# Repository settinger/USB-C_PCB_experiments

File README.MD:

# USB-C PCB Experiments

This is part of an ongoing series of projects involving creative interpretations of the USB mechanical standards. You've probably seen [2.0mm thick PCBs that fit in USB ports](http://digistump.com/products/1), and maybe you've seen [0.6mm thick PCBs that fit in USB-Micro cables](https://twitter.com/DHammarskjold/status/1285291152602796032). So what about USB-C? T​he plastic tab inside a USB-C port is about 0.7mm thick. I think [bobricius](https://hackaday.io/bobricius) has had success using 0.8mm thick PCBs; 0.6mm thick PCBs are way too loose. I haven't found a fab that will do 0.7mm (or 28 mil) PCBs unless you special-order an entire panel.​

So, what other ways are there to reach 0.7mm thickness? My original plan was to join an 0.1mm flex PCB and an 0.6mm FR4 PCB, but then I realized: you know what else is 0.6mm thick? The ATtiny84A BGA package. Granted, there are only contacts on one side of the PCB, but that shouldn't matter with the symmetric USB-C pinout, right? ...Right? (foreshadowing)

The 3mm-square ATtiny acts as a stiffener for the flex PCB, and it comes out to 0.7mm on the dot! I only have an imperial set of calipers as seen above. The dial shows 0.0275 inches, which is 0.6985 millimeters. ~~So this is looking pretty promising.~~ After [my initial tests](https://twitter.com/DHammarskjold/status/1476667605746270224), I am leaning toward a circuit sandwiched between two PCBs. The result is about 0.85mm thick with OSH Park flex PCBs, so I may need to locate another vendor.

What would you do with an ATtiny that lives inside your USB-C cable? I have a few ideas for demonstrations at the moment.

## Demo 1: RGB LED that can't be programmed over USB

There are two revisions of this design; the schematics are in the repo as `rgb_no_bootloader.kicad_sch` and `rgb_no_bootloader_r2.kicad_sch`. Revision 1 is the one that I have assembled and ready to work with, it's also the one I would like some code help with! My current code is in the in the code folder as `demo_1_revision_1`; it is saved as an Arduino .ino file but it should work fine with AVR-GCC without any changes.

This demo is as simple as possible: the microcontroller controlls an RGB LED that juuuust barely pokes out of the USB-C cable plug. It has to be programmed using that 8-pin FFC connector, and then the FFC connector has to be snipped off in order to use the dang thing. Right now I have one fully-soldered version of revision 1, ~~but I haven't cut the FFC connector yet because I would like some help improving the code.~~

Demo 1 Revision 2 is necessary because, on revision 1, the RGB LED is *not* connected to the Fast-PWM-enabled pins on the microcontroller. As a result I have to use [binary code modulation](http://www.batsocks.co.uk/readme/art_bcm_3.htm) to achieve any sort of brightness control. It's working alright, [as shown here](https://twitter.com/DHammarskjold/status/1475741148522049536), ~~but I'm not confident enough with the code to chop off the programming connector yet.~~

When I finally removed the connector, I documented it [in this Twitter thread](https://twitter.com/DHammarskjold/status/1476667605746270224). I got excited and tried putting it in a powered USB cable while the top side was exposed. Unsurprisingly, this caused some shorts and some damage! I soldered in a new RGB LED and applied conformal coating. The conformal coating helped for a little while, but got scraped away pretty quickly. This suggests to me that any future designs will need to be sandwiched between *two* PCBs.

As you can see, there is a large tab sticking out so I can grab and remove the PCB from the cable. However, out of spite for, uh, myself, I have labelled it the "cowards' tab." Past me was encouraging present me to remove that tab and make the board impossible to remove, thereby turning a useful cable into a cute little art piece for all eternity.

## Demo 2: ~~R~~GB LED that *can* be programmed over USB

It would be nice to use the USB data lines to program the microcontroller! I didn't attempt this for the first revision because I wanted to keep the board as uncluttered and simple as possible. It will result in a denser board that may need more careful soldering, but it should be possible! Well, *mostly* possible. I didn't find a way to route red green and blue at the same time, so I've omitted red from the design.

As I understand it, I need to add at least five extra components: a pullup for the D- line, small resistors on the D- and D+ lines, and zener diodes as level shifters. This is the low-complexity approach used on the Digispark and its derivatives. I have not attempted to make this board yet. Also, look at the 3d render above; doesn't it look like an owl? I love it.

There is an interesting issue, however. In the USB-C standard, the D+/D- lines are only connected on one side of the plug! It assumes that the USB-C port has D+/D- connectors on both sides, so the plug orientation should not matter. But our USB-C port only has D+/D- connectors on one side. We've reintroduced the classic USB behavior of having to flip the device over 3 times before it works!

## Demo 3: Basically a Digispark but smaller

In this version, the FFC portion is meant to stay attached! And all the components are 0402-sized with generous spacing so I can worry less when soldering. As a result it can be used in a slightly more "normal" fashion—still operable by sticking it inside a USB-C cable, but now there's a breakout of sorts.

## Demo 4: "Coulda used a 555"

On the Hackaday websites, "Coulda used a 555" is shorthand for grumpy commenters who criticize designs that they consider inelegant, for example, using a microcontroller where a 555 would suffice. In the past I've poked fun at this notion by, among other things, using *three* microcontrollers where a 555 would suffice, and using a 555 Schmitt Trigger where a single SPST button would suffice. As luck would have it, there is a BGA 555 IC that is just shy of 0.6mm tall! I've had to pair it with a 10μF capacitor that is a bit taller, but it's a fun idea to explore later.

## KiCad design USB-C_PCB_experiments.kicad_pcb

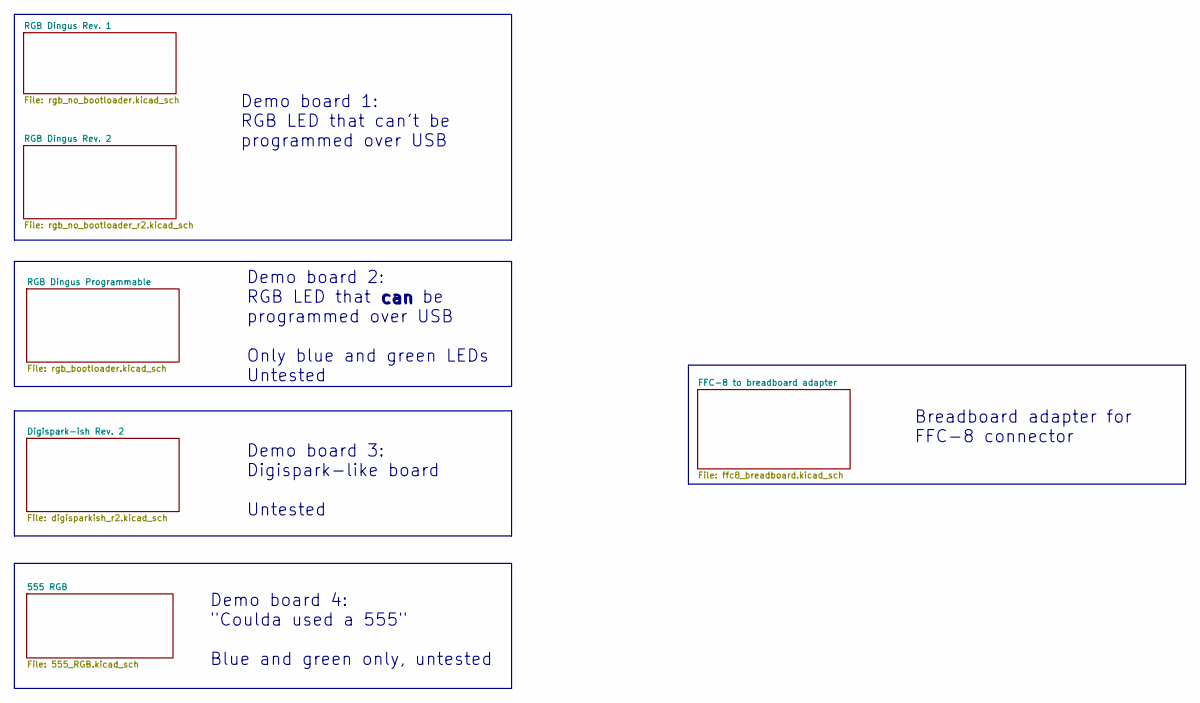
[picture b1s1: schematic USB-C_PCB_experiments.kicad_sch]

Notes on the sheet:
Breadboard adapter for FFC-8 connector
Demo board 1: RGB LED that can't be programmed over USB
Demo board 4: "Coulda used a 555" Blue and green only, untested
Demo board 3: Digispark-like board Untested
can
Demo board 2: RGB LED that can be programmed over USB Only blue and green LEDs Untested

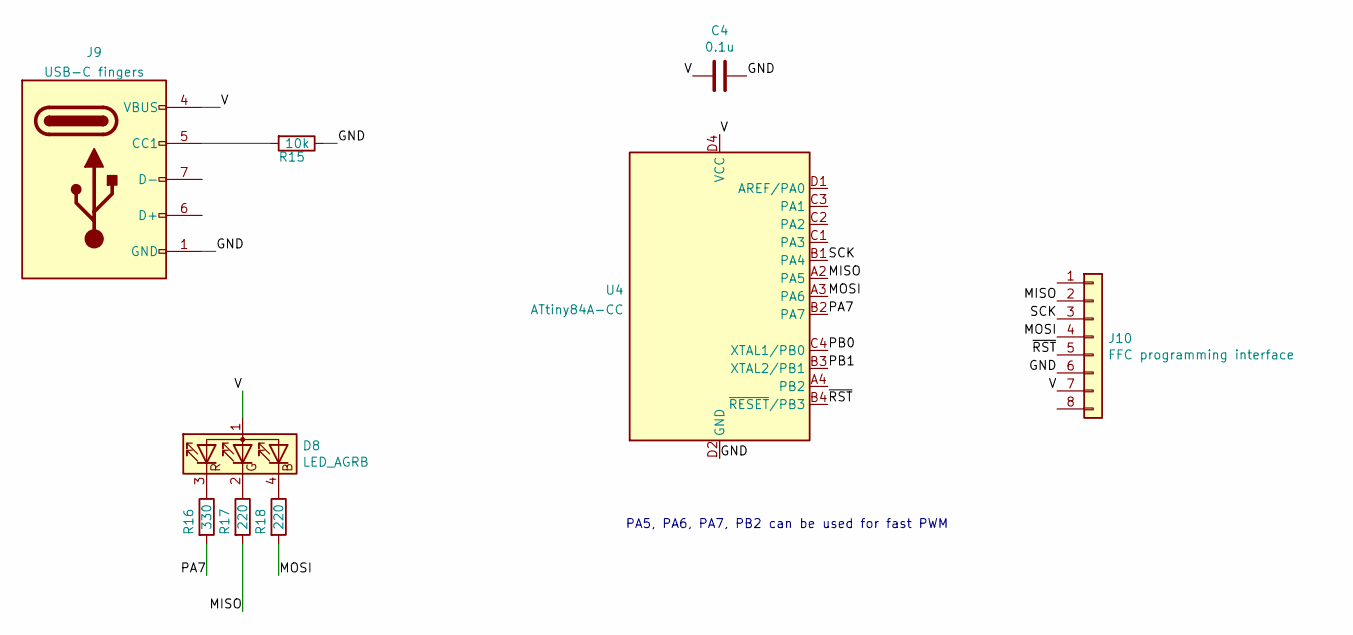
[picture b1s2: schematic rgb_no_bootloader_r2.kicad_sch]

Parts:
C4: 0.1u; C_0201_0603Metric
D8: LED_AGRB; LED_everlight_EASV2713RGBA1
J9: USB-C fingers
J10: FFC programming interface; FFC-08
R15: 10k; R_0201_0603Metric
R16: 330; R_0201_0603Metric
R17, R18: 220; R_0201_0603Metric
U4: ATtiny84A-CC; UFBGA-15_3.0x3.0mm_Layout4x4_P0.65mm

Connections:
/RGB Dingus Rev. 2/GND: C4.1, J9.1 (GND), J9.12 (GND), J10.6, R15.1, U4.D2 (GND), U4.D3 (GND)
/RGB Dingus Rev. 2/MISO: J10.2, R17.2, U4.A2 (PA5)
/RGB Dingus Rev. 2/MOSI: J10.4, R18.2, U4.A3 (PA6)
/RGB Dingus Rev. 2/PA7: R16.2, U4.B2 (PA7)
/RGB Dingus Rev. 2/PB0: U4.C4 (XTAL1/PB0)
/RGB Dingus Rev. 2/PB1: U4.B3 (XTAL2/PB1)
/RGB Dingus Rev. 2/SCK: J10.3, U4.B1 (PA4)
/RGB Dingus Rev. 2/V: C4.2, D8.1 (A), J9.4 (VBUS), J9.9 (VBUS), J10.7, U4.D4 (VCC)
/RGB Dingus Rev. 2/~RST: J10.5, U4.B4 (~RESET/PB3)
unnamed: D8.2 (GK), R17.1
unnamed: D8.3 (RK), R16.1
unnamed: D8.4 (BK), R18.1
unnamed: J9.5 (CC1), R15.2

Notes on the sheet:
PA5, PA6, PA7, PB2 can be used for fast PWM

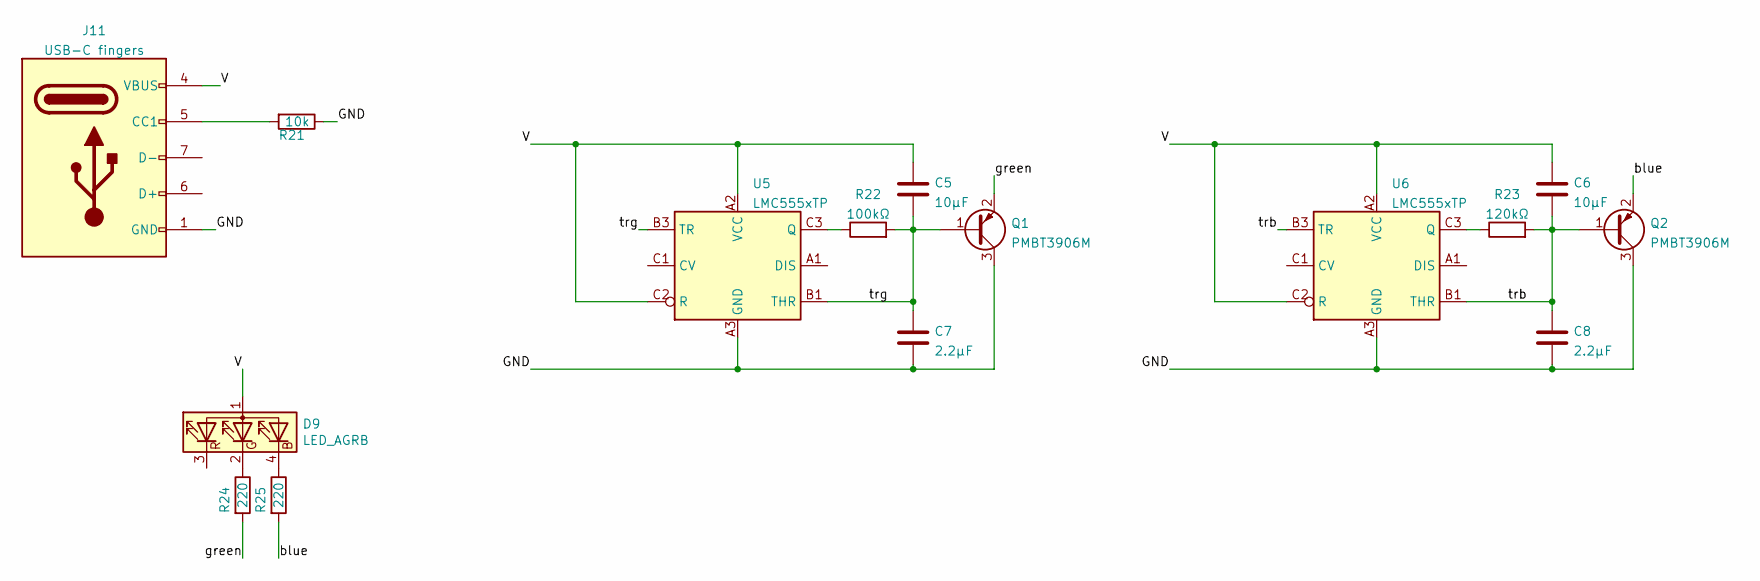
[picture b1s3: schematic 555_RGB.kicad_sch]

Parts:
C5, C6: 10μF; C_0402_1005Metric
C7, C8: 2.2μF; C_0201_0603Metric
D9: LED_AGRB; LED_everlight_EASV2713RGBA1
J11: USB-C fingers
Q1, Q2: PMBT3906M; SOT-883
R21: 10k; R_0201_0603Metric
R22: 100kΩ; R_0201_0603Metric
R23: 120kΩ; R_0201_0603Metric
R24, R25: 220; R_0201_0603Metric
U5, U6: LMC555xTP; Texas_DSBGA-8_1.43x1.41mm_Layout3x3_P0.5mm

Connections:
/555 RGB/GND: C7.2, C8.2, J11.1 (GND), J11.12 (GND), Q1.3 (C), Q2.3 (C), R21.1, U5.A3 (GND), U6.A3 (GND)
/555 RGB/V: C5.1, C6.1, D9.1 (A), J11.4 (VBUS), J11.9 (VBUS), U5.A2 (VCC), U5.C2 (R), U6.A2 (VCC), U6.C2 (R)
/555 RGB/blue: Q2.2 (E), R25.2
/555 RGB/green: Q1.2 (E), R24.2
/555 RGB/trb: C6.2, C8.1, Q2.1 (B), R23.2, U6.B1 (THR), U6.B3 (TR)
/555 RGB/trg: C5.2, C7.1, Q1.1 (B), R22.2, U5.B1 (THR), U5.B3 (TR)
unnamed: D9.2 (GK), R24.1
unnamed: D9.4 (BK), R25.1
unnamed: J11.5 (CC1), R21.2
unnamed: R22.1, U5.C3 (Q)
unnamed: R23.1, U6.C3 (Q)

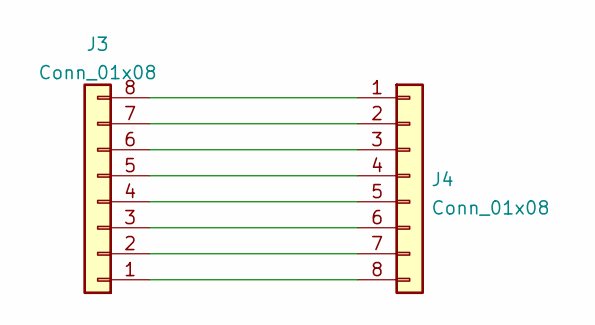
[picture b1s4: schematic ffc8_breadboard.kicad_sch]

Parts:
J3: Conn_01x08
J4: Conn_01x08; PinHeader_1x08_P2.54mm_Vertical

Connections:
unnamed: J3.1, J4.8
unnamed: J3.2, J4.7
unnamed: J3.3, J4.6
unnamed: J3.4, J4.5
unnamed: J3.5, J4.4
unnamed: J3.6, J4.3
unnamed: J3.7, J4.2
unnamed: J3.8, J4.1

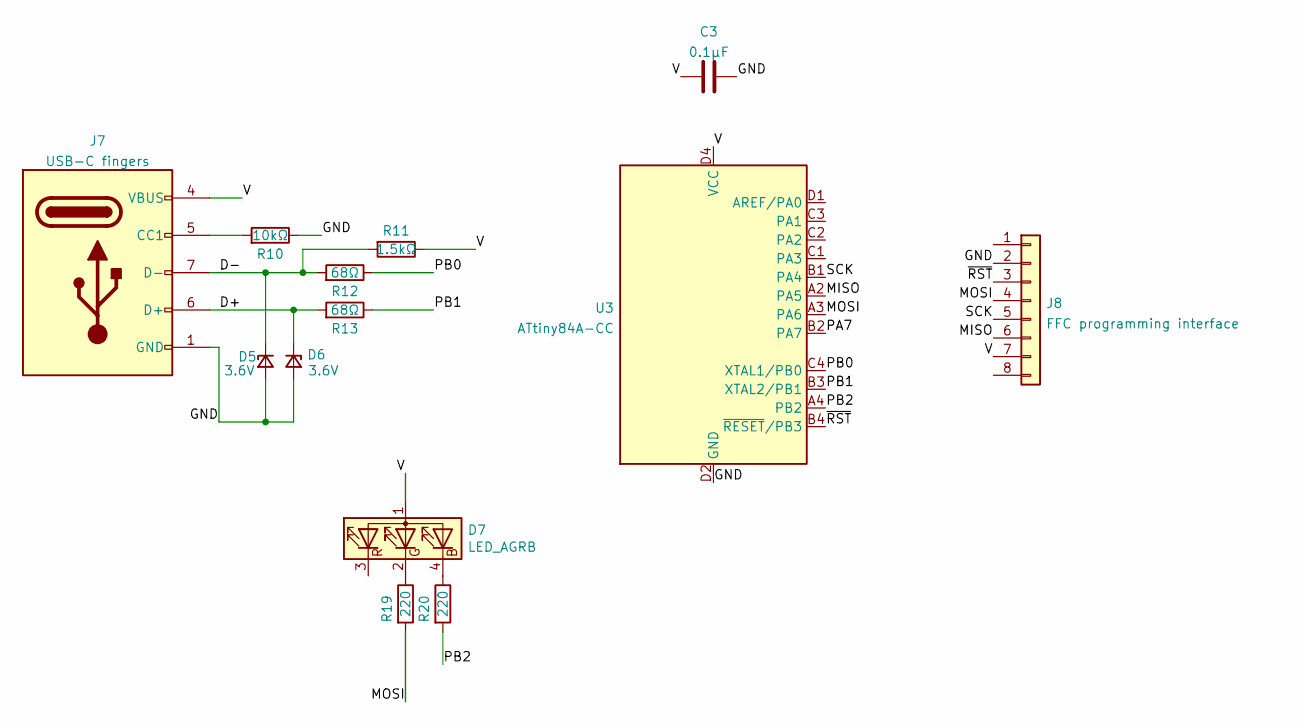
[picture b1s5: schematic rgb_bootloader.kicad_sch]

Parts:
C3: 0.1μF; C_0402_1005Metric
D5, D6: 3.6V; D_0402_1005Metric
D7: LED_AGRB; LED_everlight_EASV2713RGBA1
J7: USB-C fingers; usb-c-one-sided
J8: FFC programming interface; FFC-08
R10: 10kΩ; R_0402_1005Metric
R11: 1.5kΩ; R_0402_1005Metric
R12, R13: 68Ω; R_0402_1005Metric
R19, R20: 220; R_0201_0603Metric
U3: ATtiny84A-CC; UFBGA-15_3.0x3.0mm_Layout4x4_P0.65mm

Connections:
/RGB Dingus Programmable/D+: D6.1 (K), J7.6 (D+), R13.2
/RGB Dingus Programmable/D-: D5.1 (K), J7.7 (D-), R11.2, R12.2
/RGB Dingus Programmable/GND: C3.1, D5.2 (A), D6.2 (A), J7.1 (GND), J7.12 (GND), J8.2, R10.1, U3.D2 (GND), U3.D3 (GND)
/RGB Dingus Programmable/MISO: J8.6, U3.A2 (PA5)
/RGB Dingus Programmable/MOSI: J8.4, R19.2, U3.A3 (PA6)
/RGB Dingus Programmable/PA7: U3.B2 (PA7)
/RGB Dingus Programmable/PB0: R12.1, U3.C4 (XTAL1/PB0)
/RGB Dingus Programmable/PB1: R13.1, U3.B3 (XTAL2/PB1)
/RGB Dingus Programmable/PB2: R20.2, U3.A4 (PB2)
/RGB Dingus Programmable/SCK: J8.5, U3.B1 (PA4)
/RGB Dingus Programmable/V: C3.2, D7.1 (A), J7.4 (VBUS), J7.9 (VBUS), J8.7, R11.1, U3.D4 (VCC)
/RGB Dingus Programmable/~RST: J8.3, U3.B4 (~RESET/PB3)
unnamed: D7.2 (GK), R19.1
unnamed: D7.4 (BK), R20.1
unnamed: J7.5 (CC1), R10.2

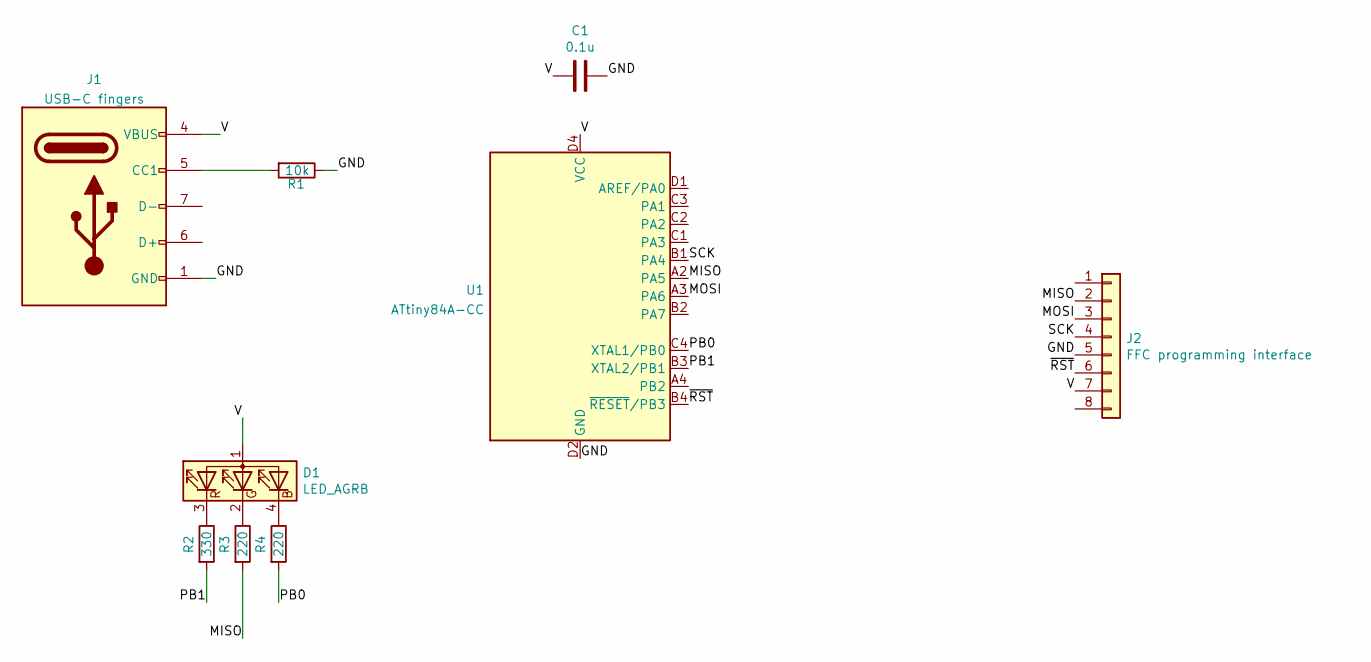
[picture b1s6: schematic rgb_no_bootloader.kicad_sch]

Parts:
C1: 0.1u; C_0201_0603Metric
D1: LED_AGRB; LED_everlight_EASV2713RGBA1
J1: USB-C fingers
J2: FFC programming interface; FFC-08
R1: 10k; R_0201_0603Metric
R2: 330; R_0201_0603Metric
R3, R4: 220; R_0201_0603Metric
U1: ATtiny84A-CC; UFBGA-15_3.0x3.0mm_Layout4x4_P0.65mm

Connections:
/RGB Dingus Rev. 1/GND: C1.1, J1.1 (GND), J1.12 (GND), J2.5, R1.1, U1.D2 (GND), U1.D3 (GND)
/RGB Dingus Rev. 1/MISO: J2.2, R3.2, U1.A2 (PA5)
/RGB Dingus Rev. 1/MOSI: J2.3, U1.A3 (PA6)
/RGB Dingus Rev. 1/PB0: R4.2, U1.C4 (XTAL1/PB0)
/RGB Dingus Rev. 1/PB1: R2.2, U1.B3 (XTAL2/PB1)
/RGB Dingus Rev. 1/SCK: J2.4, U1.B1 (PA4)
/RGB Dingus Rev. 1/V: C1.2, D1.1 (A), J1.4 (VBUS), J1.9 (VBUS), J2.7, U1.D4 (VCC)
/RGB Dingus Rev. 1/~RST: J2.6, U1.B4 (~RESET/PB3)
unnamed: D1.2 (GK), R3.1
unnamed: D1.3 (RK), R2.1
unnamed: D1.4 (BK), R4.1
unnamed: J1.5 (CC1), R1.2

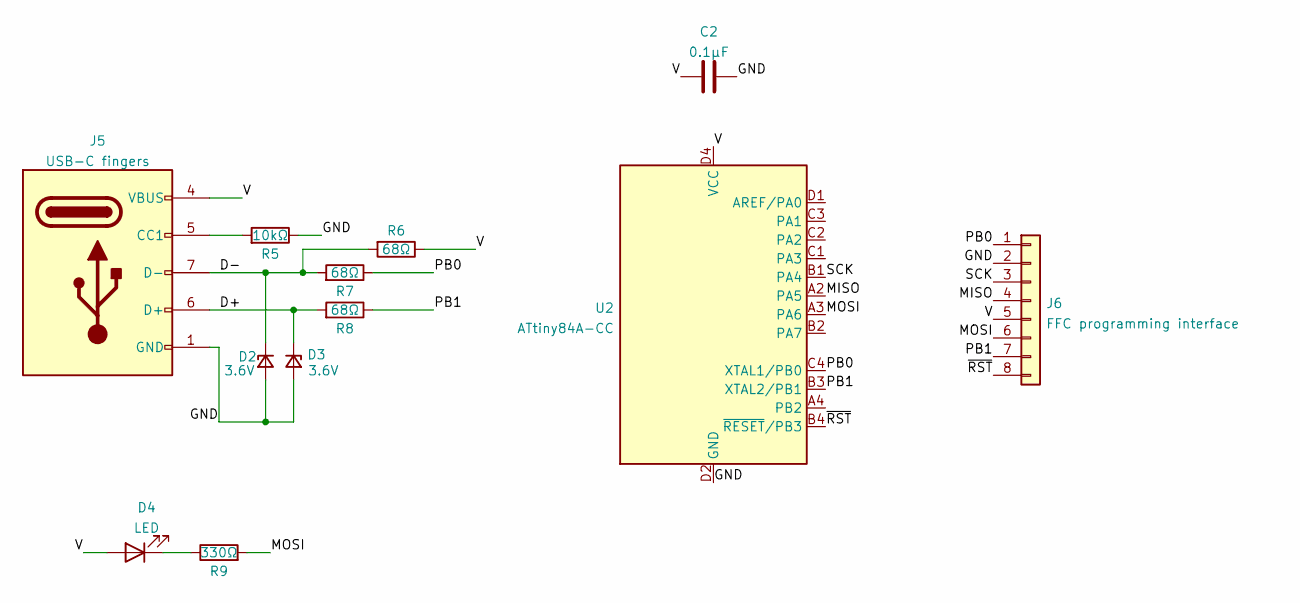
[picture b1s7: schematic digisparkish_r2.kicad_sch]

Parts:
C2: 0.1μF; C_0402_1005Metric
D2, D3: 3.6V; D_0402_1005Metric
D4: LED; LED_0402_1005Metric
J5: USB-C fingers; usb-c-one-sided
J6: FFC programming interface; FFC-08
R5: 10kΩ; R_0402_1005Metric
R6, R7, R8: 68Ω; R_0402_1005Metric
R9: 330Ω; R_0402_1005Metric
U2: ATtiny84A-CC; UFBGA-15_3.0x3.0mm_Layout4x4_P0.65mm

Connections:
/Digispark-ish Rev. 2/D+: D3.1 (K), J5.6 (D+), R8.2
/Digispark-ish Rev. 2/D-: D2.1 (K), J5.7 (D-), R6.2, R7.2
/Digispark-ish Rev. 2/GND: C2.1, D2.2 (A), D3.2 (A), J5.1 (GND), J5.12 (GND), J6.2, R5.1, U2.D2 (GND), U2.D3 (GND)
/Digispark-ish Rev. 2/MISO: J6.4, U2.A2 (PA5)
/Digispark-ish Rev. 2/MOSI: J6.6, R9.2, U2.A3 (PA6)
/Digispark-ish Rev. 2/PB0: J6.1, R7.1, U2.C4 (XTAL1/PB0)
/Digispark-ish Rev. 2/PB1: J6.7, R8.1, U2.B3 (XTAL2/PB1)
/Digispark-ish Rev. 2/SCK: J6.3, U2.B1 (PA4)
/Digispark-ish Rev. 2/V: C2.2, D4.2 (A), J5.4 (VBUS), J5.9 (VBUS), J6.5, R6.1, U2.D4 (VCC)
/Digispark-ish Rev. 2/~RST: J6.8, U2.B4 (~RESET/PB3)
unnamed: D4.1 (K), R9.1
unnamed: J5.5 (CC1), R5.2

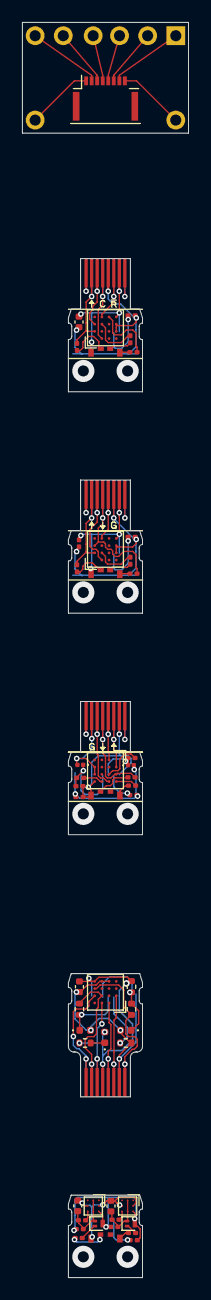
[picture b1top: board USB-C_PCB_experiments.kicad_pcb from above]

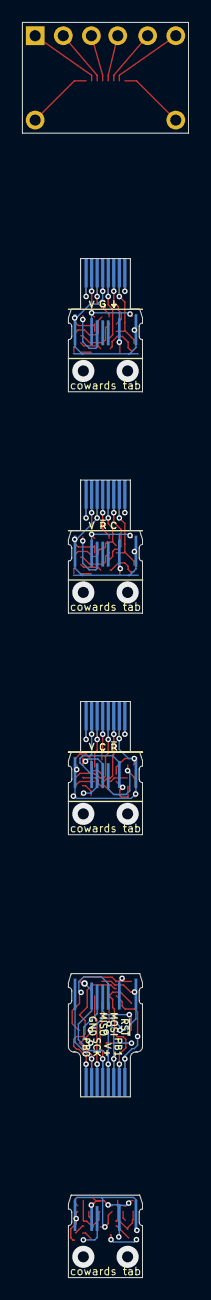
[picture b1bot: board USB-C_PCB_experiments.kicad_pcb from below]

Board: 2 copper layers, 15.0 x 113.4 mm, 60 parts (5 on the bottom side), 68 nets.

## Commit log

2021-12-30 Initial public release
2021-12-30 Oh I guess you can't put Youtube embeds in markdown on GH?
2022-01-20 Finished routing Demo 2, added Demo 4, updated readme with newer findings
